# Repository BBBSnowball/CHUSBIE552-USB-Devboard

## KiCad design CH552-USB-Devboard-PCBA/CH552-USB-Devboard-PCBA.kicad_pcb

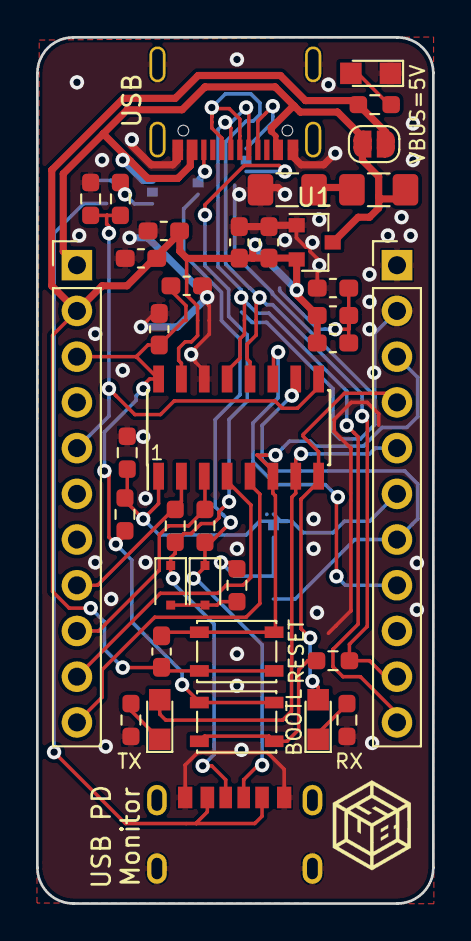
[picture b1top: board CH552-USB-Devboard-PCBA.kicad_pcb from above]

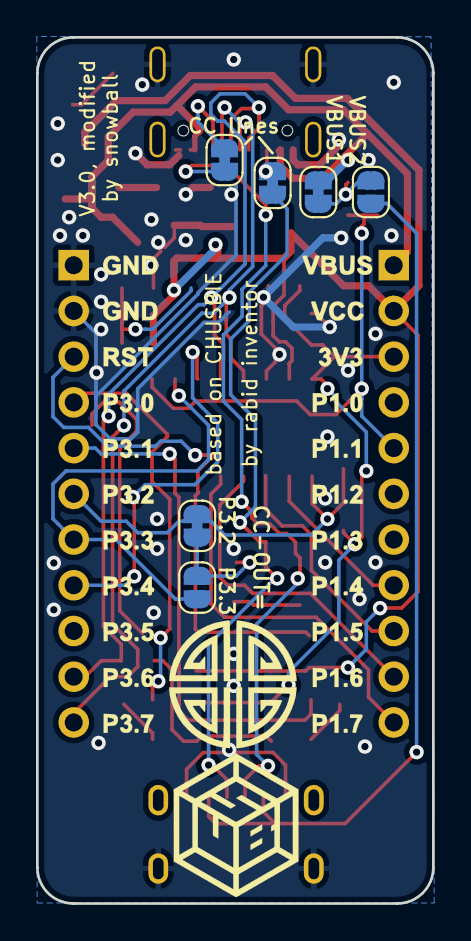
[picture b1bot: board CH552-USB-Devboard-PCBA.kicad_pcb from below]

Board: 2 copper layers, 22.0 x 48.1 mm, 43 parts (6 on the bottom side), 31 nets.

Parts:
C1, C2, C3, C9: 100nF; C_0603_1608Metric_Pad1.05x0.95mm_HandSolder
C4, C7: DNP/1uF; C_0603_1608Metric_Pad1.05x0.95mm_HandSolder
C5, C6: 4u7, 50V; C_1206_3216Metric_Pad1.42x1.75mm_HandSolder
C8: 10nF; C_0603_1608Metric_Pad1.05x0.95mm_HandSolder
C10: 10uF; C_0603_1608Metric_Pad1.05x0.95mm_HandSolder
D1, D2: LED, yellow; LED_0805
D3: LED, green?; LED_0805
D4, D5: e.g. 1N4148, C917006, C708767; D_SOD-323F
J1, J2: Conn_01x11_Male; PinHeader_1x11_P2.54mm_Vertical
J3: USB_C_Receptacle; VACON_CSP_USC16_TR
J4: USB_C_Receptacle; Korean-Hroparts-Elec-TYPE-C-31-M-17
JP1, JP3, JP8: Jumper; SolderJumper-2_P1.3mm_Open_RoundedPad1.0x1.5mm
JP2, JP5, JP6, JP7: Jumper; SolderJumper-2_P1.3mm_Bridged_RoundedPad1.0x1.5mm
R1, R2: 68; R_0603_1608Metric_Pad0.98x0.95mm_HandSolder
R3, R4, R5, R9, R12: 10k; R_0603_1608Metric_Pad0.98x0.95mm_HandSolder
R6: 22k; R_0603_1608Metric_Pad0.98x0.95mm_HandSolder
R7: 220; R_0603_1608Metric_Pad0.98x0.95mm_HandSolder
R8, R10: 1k; R_0603_1608Metric_Pad0.98x0.95mm_HandSolder
R11: 62k; R_0603_1608Metric_Pad1.05x0.95mm_HandSolder
R13: 22k; R_0603_1608Metric_Pad1.05x0.95mm_HandSolder
SW1, SW2: SW_Push; SW_SPST_PTS810
U1: ZXTR2105FQ; SOT-23
U2: CH552G; SOIC-16_3.9x9.9mm_Pitch1.27mm

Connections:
+3V3: C2.1, C7.1, J1.3, R9.2, SW1.1, U2.16
/CC1: D4.1, J4.A5, JP5.2, R1.1
/CC2: D5.1, J4.B5, JP6.2, R2.1
/P1.1: J1.5, R10.1, R12.1, U2.9
/P1.4: J1.8, R1.2, U2.2
/P1.5: J1.9, R2.2, U2.3
/P1.6: J1.10, U2.4
/P1.7: J1.11, U2.5
/P3.0: D1.2, J2.4, U2.8
/P3.1: D2.2, J2.5, U2.7
/P3.2: J2.6, JP2.2, R8.1, R9.1, U2.1
/P3.3: J2.7, JP3.2, U2.10
/P3.4: J2.8, U2.11
/P3.6: J2.10, J3.A6, J3.B6, R6.1, U2.12
/P3.7: J2.11, J3.A7, J3.B7, U2.13
/RESET: C3.2, J2.3, SW2.1, U2.6
/VBUS2: J4.A9, J4.B9, JP8.1
GND: C1.2, C2.2, C4.2, C6.2, C7.2, C9.2, C10.2, D3.1, J2.1, J2.2, J3.A1, J3.A12, J3.B1, J3.B12, J3.S1, J4.A12, J4.B12, J4.S1, R3.1, R4.1, R8.2, R10.2, R13.1, U1.1, U2.14
unnamed: C5.2, C6.1
unnamed: C8.2, R11.1, R13.2
unnamed: D1.1, R3.2
unnamed: D2.1, R4.2
unnamed: D3.2, R5.2
unnamed: D4.2, D5.2, R7.2
unnamed: J3.A5, JP5.1
unnamed: J3.B5, JP6.1
unnamed: JP2.1, JP3.1, R7.1
unnamed: JP7.2, JP8.2, R12.2
unnamed: R6.2, SW1.2
VBUS: C5.1, J1.1, J3.A4, J3.A9, J3.B4, J3.B9, JP1.1, JP7.1, U1.3
VCC: C1.1, C3.1, C4.1, C8.1, C9.1, C10.1, J1.2, JP1.2, R5.1, R11.2, SW2.2, U1.2, U2.15

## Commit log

2021-05-14 add resistors for BOOTL and CC lines, remove LDO
2021-05-16 add reference voltage for ACMP, replace symbol for USB connector
    That symbol was causing warnings because some of the pins are not
    available on the footprint. Kicad has the appropriate symbol so
    let's use that.
2021-05-16 add ibom for v2.0
2021-05-16 add voltage divider for VBUS, optimize GND plane
2021-05-18 add 2nd USB connector, dedicated to PD monitoring
2021-06-12 add LCSC part numbers
2021-06-12 clean up schematic
2021-06-12 stop using the rescue library
2021-06-12 add LDO for VCC (5V)
    It supports VBUS up to 48V because that's what future USB PD will
    use and we want to support that.
2021-06-14 update PCB
2021-06-14 some small changes for the PCB
2021-06-16 fixes
2021-06-16 make copy for PCBA
2021-06-16 create variant for PCBA
2021-06-16 add PCBA files
2021-06-17 replace LDO
    I'm quite sure it wasn't out of stock three days ago...
2021-06-17 adjust rotation of LDO
